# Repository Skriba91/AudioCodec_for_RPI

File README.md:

# Audio CODECs for Raspberry Pi

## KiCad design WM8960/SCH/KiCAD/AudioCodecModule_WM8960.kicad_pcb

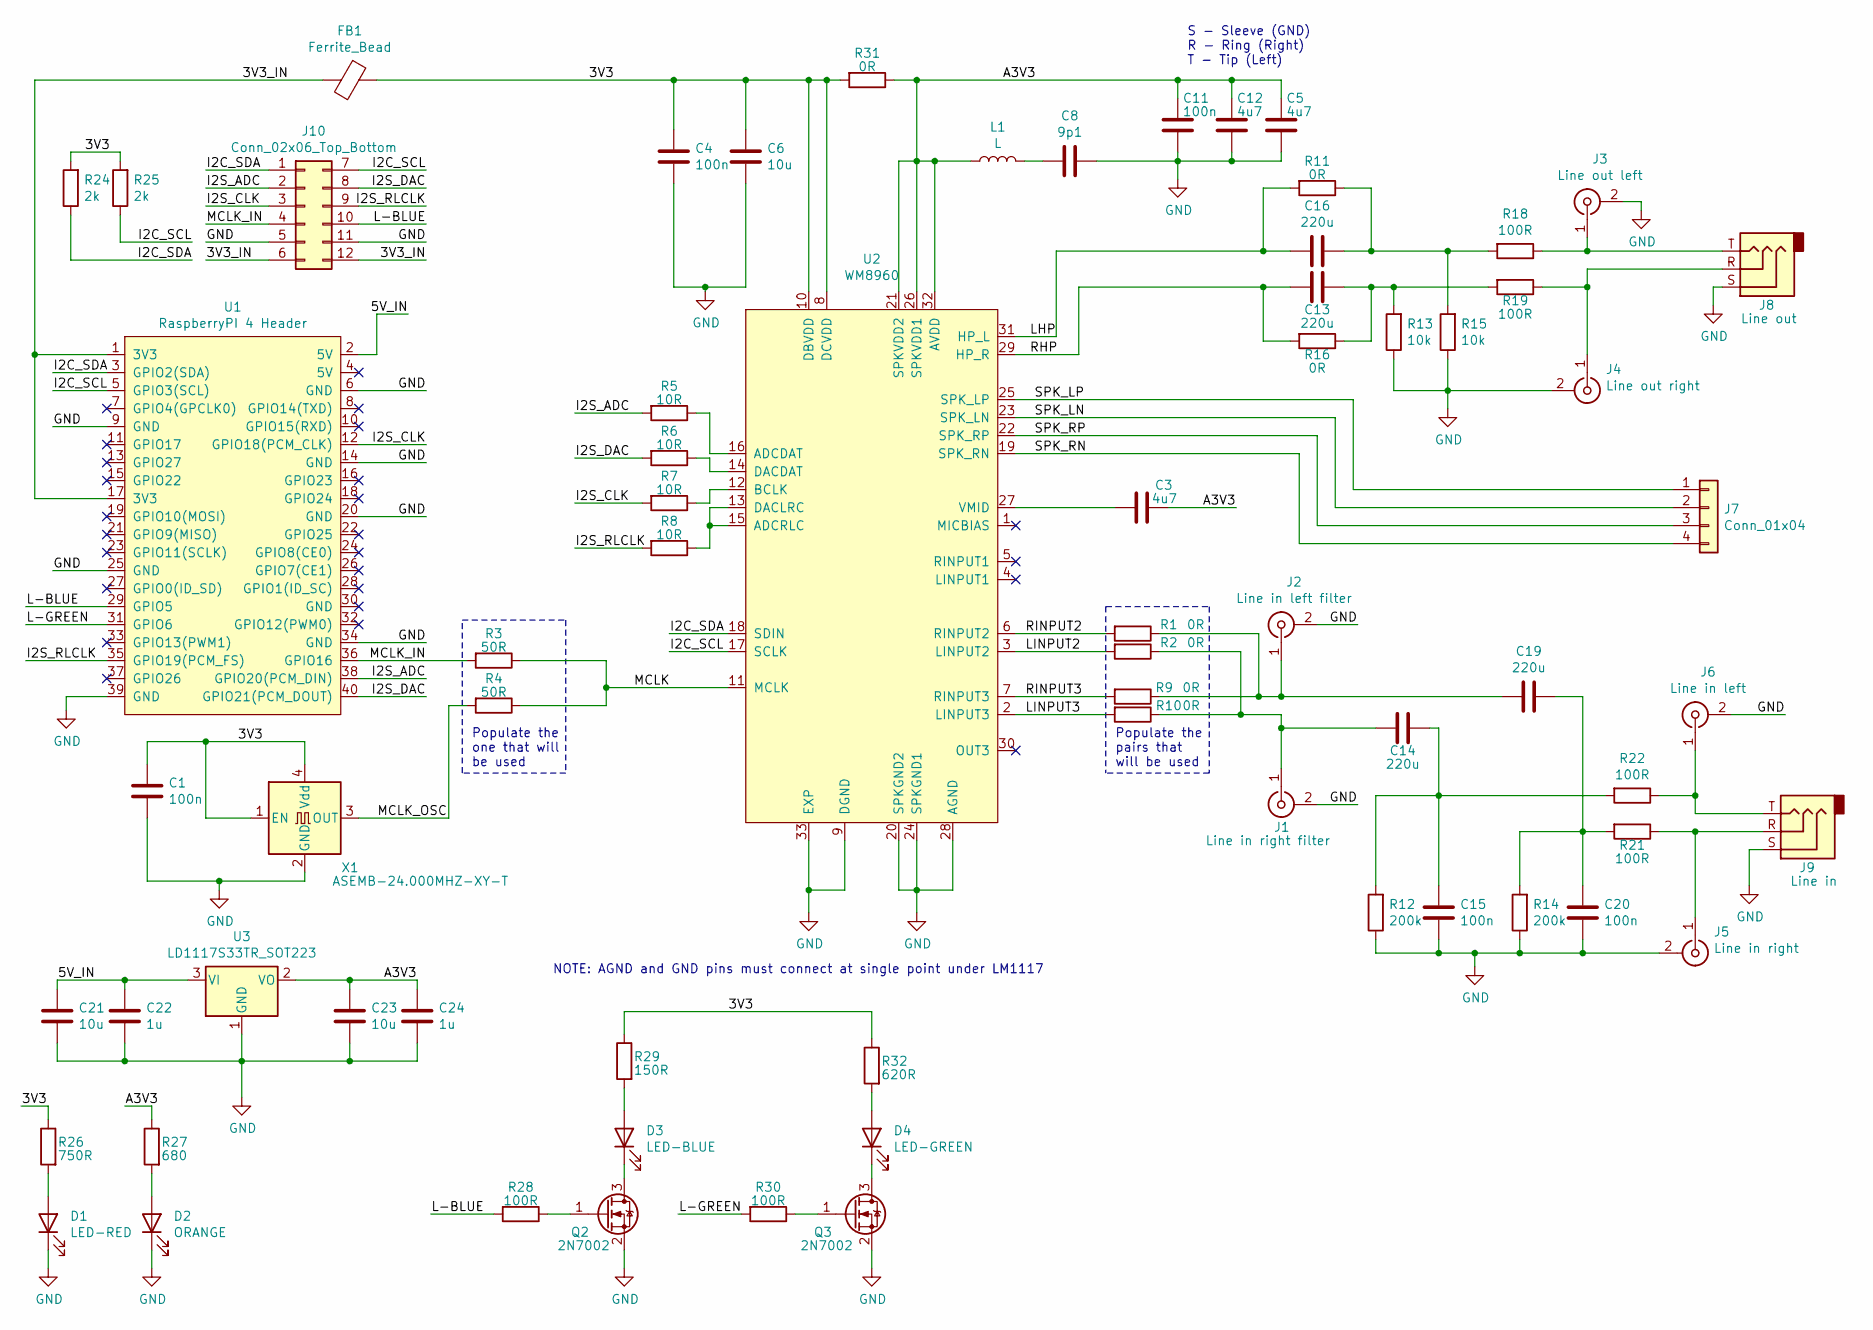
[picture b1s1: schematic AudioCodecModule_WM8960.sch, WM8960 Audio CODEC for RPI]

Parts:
C1, C4, C11, C15, C20: 100n; C_0603_1608Metric_Pad1.05x0.95mm_HandSolder
C3, C5, C12: 4u7; C_0603_1608Metric_Pad1.05x0.95mm_HandSolder
C6: 10u; C_1206_3216Metric_Pad1.42x1.75mm_HandSolder
C8: 9p1; C_0603_1608Metric_Pad1.05x0.95mm_HandSolder
C13, C14, C16, C19: 220u; C_1206_3216Metric_Pad1.42x1.75mm_HandSolder
C21, C23: 10u; C_0603_1608Metric_Pad1.05x0.95mm_HandSolder
C22, C24: 1u; C_0603_1608Metric_Pad1.05x0.95mm_HandSolder
D1: LED-RED; LED_0805_2012Metric_Pad1.15x1.40mm_HandSolder
D2: ORANGE; LED_0805_2012Metric_Pad1.15x1.40mm_HandSolder
D3: LED-BLUE; LED_0805_2012Metric_Pad1.15x1.40mm_HandSolder
D4: LED-GREEN; LED_0805_2012Metric_Pad1.15x1.40mm_HandSolder
FB1: Ferrite_Bead; L_0603_1608Metric_Pad1.05x0.95mm_HandSolder
J1: Line in right filter; SMA_Amphenol_132134-11_Vertical
J2: Line in left filter; SMA_Amphenol_132134-11_Vertical
J3: Line out left; SMA_Amphenol_132134-11_Vertical
J4: Line out right; SMA_Amphenol_132134-11_Vertical
J5: Line in right; SMA_Amphenol_132134-11_Vertical
J6: Line in left; SMA_Amphenol_132134-11_Vertical
J7: Conn_01x04; PinHeader_1x04_P2.54mm_Vertical
J8: Line out; Jack_3.5mm_Ledino_KB3SPRS_Horizontal
J9: Line in; Jack_3.5mm_Ledino_KB3SPRS_Horizontal
J10: Conn_02x06_Top_Bottom; PinHeader_2x06_P2.54mm_Horizontal
L1: L; L_1206_3216Metric_Pad1.42x1.75mm_HandSolder
Q2, Q3: 2N7002; SOT-23
R1, R2, R9, R10, R11, R16, R31: 0R; R_0603_1608Metric_Pad1.05x0.95mm_HandSolder
R3, R4: 50R; R_0603_1608Metric_Pad1.05x0.95mm_HandSolder
R5, R6, R7, R8: 10R; R_0603_1608Metric_Pad1.05x0.95mm_HandSolder
R12, R14: 200k; R_0603_1608Metric_Pad1.05x0.95mm_HandSolder
R13, R15: 10k; R_0603_1608Metric_Pad1.05x0.95mm_HandSolder
R18, R19, R21, R22, R28, R30: 100R; R_0603_1608Metric_Pad1.05x0.95mm_HandSolder
R24, R25: 2k; R_0603_1608Metric_Pad1.05x0.95mm_HandSolder
R26: 750R; R_0603_1608Metric_Pad1.05x0.95mm_HandSolder
R27: 680; R_0603_1608Metric_Pad1.05x0.95mm_HandSolder
R29: 150R; R_0603_1608Metric_Pad1.05x0.95mm_HandSolder
R32: 620R; R_0603_1608Metric_Pad1.05x0.95mm_HandSolder
U1: RaspberryPI 4 Header; PinHeader_2x20_P2.54mm_Vertical
U2: WM8960; QFN-32-1EP_5x5mm_P0.5mm_EP3.1x3.1mm_ThermalVias
U3: LD1117S33TR_SOT223; SOT-223-3_TabPin2
X1: ASEMB-24.000MHZ-XY-T; Oscillator_SMD_Abracon_ASE-4Pin_3.2x2.5mm

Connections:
/3V3: C1.2, C4.2, C6.1, FB1.1, R24.2, R25.2, R26.1, R29.1, R31.2, R32.1, U2.8 (DCVDD), U2.10 (DBVDD), X1.1 (EN), X1.4 (Vdd)
/3V3_IN: FB1.2, J10.6, J10.12, U1.1 (3V3), U1.17 (3V3)
/5V_IN: C21.1, C22.1, U1.2 (5V), U3.3 (VI)
/A3V3: C3.2, C5.1, C11.2, C12.1, C23.1, C24.1, L1.1, R27.1, R31.1, U2.21 (SPKVDD2), U2.26 (SPKVDD1), U2.32 (AVDD), U3.2 (VO)
/I2C_SCL: J10.7, R25.1, U1.5 (GPIO3(SCL)), U2.17 (SCLK)
/I2C_SDA: J10.1, R24.1, U1.3 (GPIO2(SDA)), U2.18 (SDIN)
/I2S_ADC: J10.2, R5.2, U1.38 (GPIO20(PCM_DIN))
/I2S_CLK: J10.3, R7.2, U1.12 (GPIO18(PCM_CLK))
/I2S_DAC: J10.8, R6.2, U1.40 (GPIO21(PCM_DOUT))
/I2S_RLCLK: J10.9, R8.2, U1.35 (GPIO19(PCM_FS))
/L-BLUE: J10.10, R28.2, U1.29 (GPIO5)
/L-GREEN: R30.2, U1.31 (GPIO6)
/LHP: C16.2, R11.2, U2.31 (HP_L)
/LINPUT2: R2.2, U2.3 (LINPUT2)
/LINPUT3: R10.2, U2.2 (LINPUT3)
/MCLK: R3.1, R4.1, U2.11 (MCLK)
/MCLK_IN: J10.4, R3.2, U1.36 (GPIO16)
/MCLK_OSC: R4.2, X1.3 (OUT)
/RHP: C13.2, R16.2, U2.29 (HP_R)
/RINPUT2: R1.2, U2.6 (RINPUT2)
/RINPUT3: R9.2, U2.7 (RINPUT3)
/SPK_LN: J7.2, U2.23 (SPK_LN)
/SPK_LP: J7.1, U2.25 (SPK_LP)
/SPK_RN: J7.4, U2.19 (SPK_RN)
/SPK_RP: J7.3, U2.22 (SPK_RP)
GND: C1.1, C4.1, C5.2, C6.2, C8.2, C11.1, C12.2, C15.2, C20.2, C21.2, C22.2, C23.2, C24.2, D1.1 (K), D2.1 (K), J1.2 (Ext), J2.2 (Ext), J3.2 (Ext), J4.2 (Ext), J5.2 (Ext), J6.2 (Ext), J8.S, J9.S, J10.5, J10.11, Q2.2 (S), Q3.2 (S), R12.1, R13.1, R14.1, R15.1, U1.6 (GND), U1.9 (GND), U1.14 (GND), U1.20 (GND), U1.25 (GND), U1.34 (GND), U1.39 (GND), U2.9 (DGND), U2.20 (SPKGND2), U2.24 (SPKGND1), U2.28 (AGND), U2.33 (EXP), U3.1 (GND), X1.2 (GND)
unnamed: C3.1, U2.27 (VMID)
unnamed: C8.1, L1.2
unnamed: C13.1, R13.2, R16.1, R19.2
unnamed: C14.1, C15.1, R12.2, R22.2
unnamed: C14.2, J1.1 (In), R2.1, R10.1
unnamed: C16.1, R11.1, R15.2, R18.2
unnamed: C19.1, C20.1, R14.2, R21.2
unnamed: C19.2, J2.1 (In), R1.1, R9.1
unnamed: D1.2 (A), R26.2
unnamed: D2.2 (A), R27.2
unnamed: D3.1 (K), Q2.3 (D)
unnamed: D3.2 (A), R29.2
unnamed: D4.1 (K), Q3.3 (D)
unnamed: D4.2 (A), R32.2
unnamed: J3.1 (In), J8.T, R18.1
unnamed: J4.1 (In), J8.R, R19.1
unnamed: J5.1 (In), J9.R, R21.1
unnamed: J6.1 (In), J9.T, R22.1
unnamed: Q2.1 (G), R28.1
unnamed: Q3.1 (G), R30.1
unnamed: R5.1, U2.16 (ADCDAT)
unnamed: R6.1, U2.14 (DACDAT)
unnamed: R7.1, U2.12 (BCLK)
unnamed: R8.1, U2.13 (DACLRC), U2.15 (ADCRLC)

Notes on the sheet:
S - Sleeve (GND) R - Ring (Right) T - Tip (Left)
Populate the one that will be used
NOTE: AGND and GND pins must connect at single point under LM1117
Populate the pairs that will be used

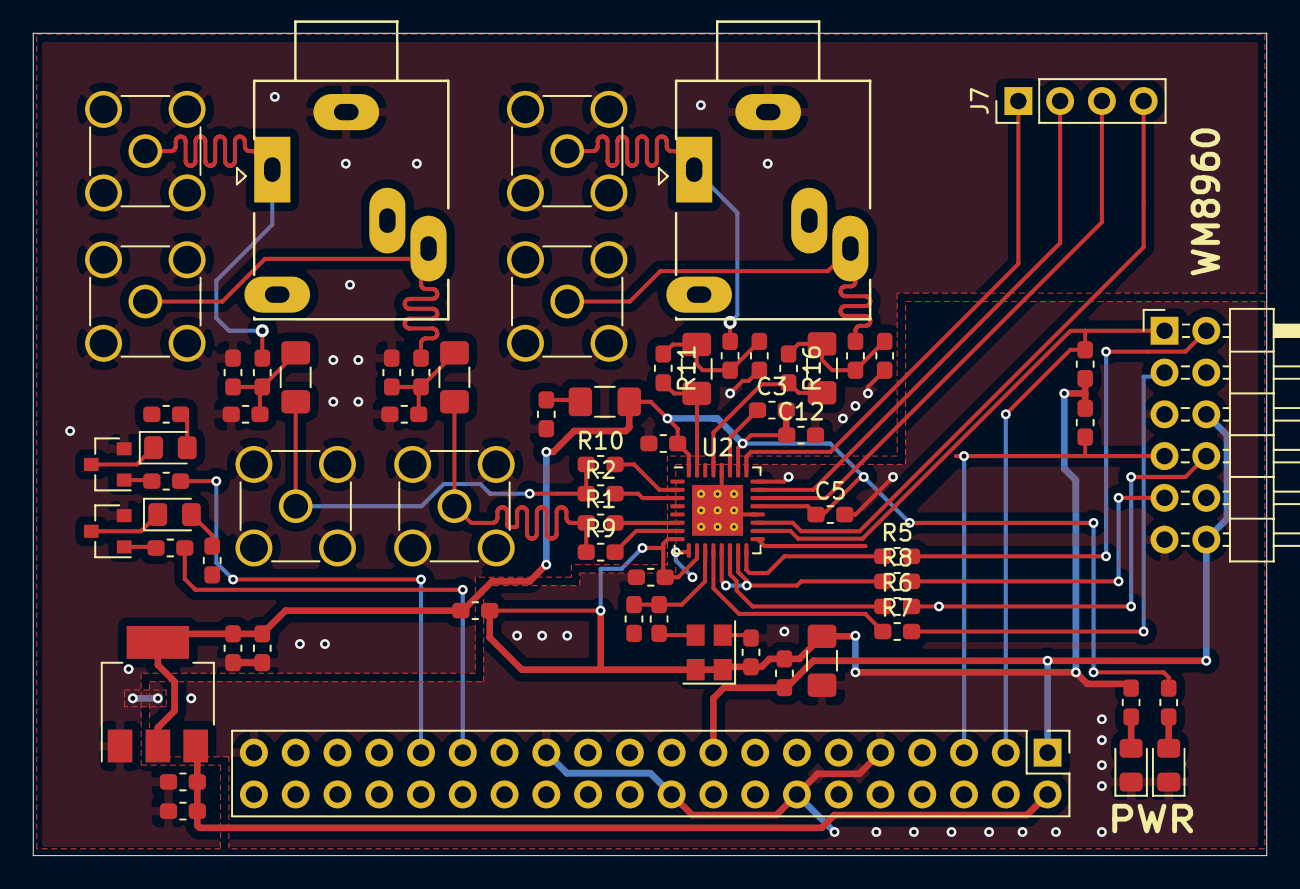
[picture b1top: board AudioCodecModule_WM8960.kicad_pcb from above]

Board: 2 copper layers, 75.0 x 50.0 mm, 69 parts (0 on the bottom side), 50 nets.

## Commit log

2021-03-22 ADAU1761 done WM8960 in progress
2021-03-22 WM8960 CODEC schematic ready
2024-06-15 ADAU1761 CAM files added
2024-06-15 WM8960 PCB added
2024-06-15 WM8960 CAM files added
2024-06-15 Board PDF added
